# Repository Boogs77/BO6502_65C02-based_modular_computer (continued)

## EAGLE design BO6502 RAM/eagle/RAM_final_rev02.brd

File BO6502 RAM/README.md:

# BO6502 RAM Module

The **RAM Module** provides the primary volatile memory storage for the BO6502 system. This revision features a highly flexible addressing logic, allowing the user to map or exclude specific memory banks through a series of onboard jumpers.

---

## 🛠 Hardware Specifications

The module is designed to interface with the 6502 bus, providing fast access to 32KB of static RAM (SRAM).

* **Base Addressing:** By default, the module is mapped to the **$0000 - $7FFF** range. This is achieved by connecting the **A15** address line to the Enable pin of the decoder logic (active when A15 is Low).
* **Clock Synchronization:** The module typically triggers with the system clock to ensure data integrity during R/W cycles. However, **JP4** allows the user to set **IC2** as "Always Enabled," bypassing the system clock trigger for specific hardware configurations.

---

## 🕹️ Jumper Configuration & Memory Mapping

This module stands out for its versatility, managed through several jumper sets:

### I/O Exclusion Jumpers
The board includes **8 dedicated jumpers** designed to "carve out" space within the $0000 - $7FFF range. This allows other peripherals (such as I/O modules) to reside in that memory space without causing bus contention with the RAM.

### Address Bank Management
* **JP1 & JP2:** These jumpers allow the physical disconnection of **A13** and **A14** lines, useful for testing or specific memory mirroring configurations.
* **High-Memory Toggle:** A specific jumper configuration allows the RAM to be remapped to the **$8000 - $FFFF** range (High Memory) instead of its default Low Memory position.

---

## 📐 Board Layout & Rendering

The Revision 02 layout features optimized traces for high-speed signal integrity and clearly labeled jumper blocks for easy configuration.

---

## 📂 Related Modules
* 🏗️ **[Backplate System](https://github.com/Boogs77/BO6502/blob/main/BO6502%20BACKPLATE/README.md)**: 39-pin system bus connection.
* 🧠 **[CPU Module](https://github.com/Boogs77/BO6502/blob/main/BO6502%20CPU/README.md)**: W65C02 central processor.
* 🖥️ **[Monitor Interface](https://github.com/Boogs77/BO6502/blob/main/BO6502%20MONITOR/README.md)**: Recommended for debugging RAM read/write operations.

---
© 2026 Boogs77 | BO6502 Project - Technical Documentation.

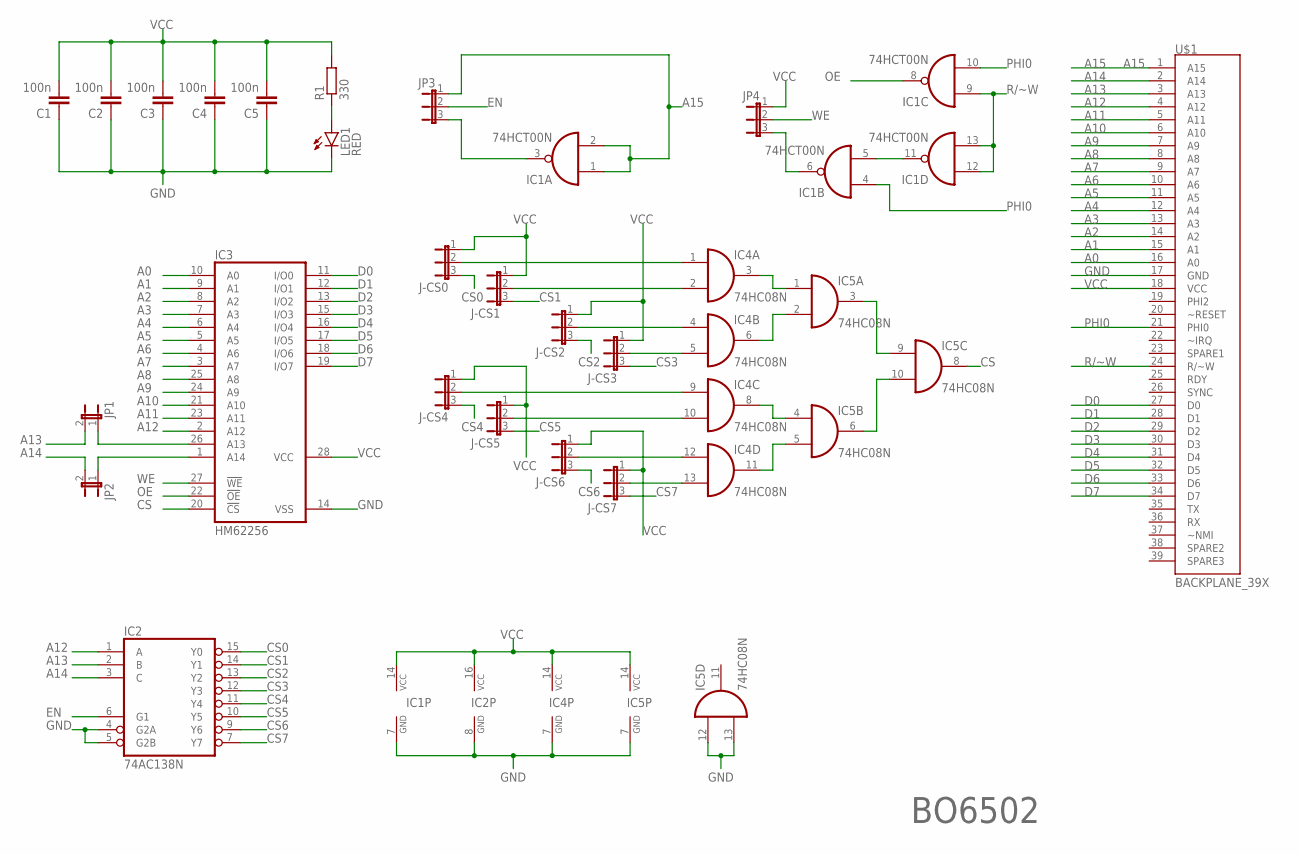
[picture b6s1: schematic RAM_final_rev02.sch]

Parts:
C1, C2, C3, C4, C5: 100n; C025-025X050
IC1: 74HCT00N; DIL14
IC2: 74AC138N; DIL16
IC3: HM62256; DIL28-6
IC4, IC5: 74HC08N; DIL14
J-CS0: J-CS0; JP2
J-CS1: J-CS1; JP2
J-CS2: J-CS2; JP2
J-CS3: J-CS3; JP2
J-CS4: J-CS4; JP2
J-CS5: J-CS5; JP2
J-CS6: J-CS6; JP2
J-CS7: J-CS7; JP2
JP1: JP1
JP2: JP2; JP1
JP3: JP3; JP2
JP4: JP4; JP2
LED1: RED; LED5MM
R1: 330; 0207/10
U$1: BACKPLANE_39X; BP_39X

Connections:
A0: IC3.10 (A0), U$1.16 (A0)
A1: IC3.9 (A1), U$1.15 (A1)
A2: IC3.8 (A2), U$1.14 (A2)
A3: IC3.7 (A3), U$1.13 (A3)
A4: IC3.6 (A4), U$1.12 (A4)
A5: IC3.5 (A5), U$1.11 (A5)
A6: IC3.4 (A6), U$1.10 (A6)
A7: IC3.3 (A7), U$1.9 (A7)
A8: IC3.25 (A8), U$1.8 (A8)
A9: IC3.24 (A9), U$1.7 (A9)
A10: IC3.21 (A10), U$1.6 (A10)
A11: IC3.23 (A11), U$1.5 (A11)
A12: IC2.1 (A), IC3.2 (A12), U$1.4 (A12)
A13: IC2.2 (B), JP1.2, U$1.3 (A13)
A14: IC2.3 (C), JP2.2, U$1.2 (A14)
A15: IC1.1 (I0), IC1.2 (I1), JP3.1, U$1.1 (A15)
CS: IC3.20 (!CS), IC5.8 (O)
CS0: IC2.15 (Y0), J-CS0.3
CS1: IC2.14 (Y1), J-CS1.3
CS2: IC2.13 (Y2), J-CS2.3
CS3: IC2.12 (Y3), J-CS3.3
CS4: IC2.11 (Y4), J-CS4.3
CS5: IC2.10 (Y5), J-CS5.3
CS6: IC2.9 (Y6), J-CS6.3
CS7: IC2.7 (Y7), J-CS7.3
D0: IC3.11 (I/O0), U$1.27 (D0)
D1: IC3.12 (I/O1), U$1.28 (D1)
D2: IC3.13 (I/O2), U$1.29 (D2)
D3: IC3.15 (I/O3), U$1.30 (D3)
D4: IC3.16 (I/O4), U$1.31 (D4)
D5: IC3.17 (I/O5), U$1.32 (D5)
D6: IC3.18 (I/O6), U$1.33 (D6)
D7: IC3.19 (I/O7), U$1.34 (D7)
EN: IC2.6 (G1), JP3.2
GND: C1.1, C2.1, C3.1, C4.1, C5.1, IC1.7 (GND), IC2.4 (G2A), IC2.5 (G2B), IC2.8 (GND), IC3.14 (VSS), IC4.7 (GND), IC5.7 (GND), IC5.12 (I0), IC5.13 (I1), LED1.K (C), U$1.17 (GND)
unnamed: IC3.26 (A13), JP1.1
unnamed: IC1.5 (I1), IC1.11 (O)
unnamed: IC1.3 (O), JP3.3
unnamed: IC1.6 (O), JP4.3
unnamed: IC4.3 (O), IC5.1 (I0)
unnamed: LED1.A, R1.1
unnamed: IC4.6 (O), IC5.2 (I1)
unnamed: IC4.8 (O), IC5.4 (I0)
unnamed: IC3.1 (A14), JP2.1
unnamed: IC4.11 (O), IC5.5 (I1)
unnamed: IC5.3 (O), IC5.9 (I0)
unnamed: IC5.6 (O), IC5.10 (I1)
unnamed: IC4.1 (I0), J-CS0.2
unnamed: IC4.2 (I1), J-CS1.2
unnamed: IC4.4 (I0), J-CS2.2
unnamed: IC4.5 (I1), J-CS3.2
unnamed: IC4.9 (I0), J-CS4.2
unnamed: IC4.10 (I1), J-CS5.2
unnamed: IC4.12 (I0), J-CS6.2
unnamed: IC4.13 (I1), J-CS7.2
OE: IC1.8 (O), IC3.22 (!OE)
PHI0: IC1.4 (I0), IC1.10 (I1), U$1.21 (PHI0)
R/~W: IC1.9 (I0), IC1.12 (I0), IC1.13 (I1), U$1.24 (R/~W)
VCC: C1.2, C2.2, C3.2, C4.2, C5.2, IC1.14 (VCC), IC2.16 (VCC), IC3.28 (VCC), IC4.14 (VCC), IC5.14 (VCC), J-CS0.1, J-CS1.1, J-CS2.1, J-CS3.1, J-CS4.1, J-CS5.1, J-CS6.1, J-CS7.1, JP4.1, R1.2, U$1.18 (VCC)
WE: IC3.27 (!WE), JP4.2

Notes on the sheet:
BO6502

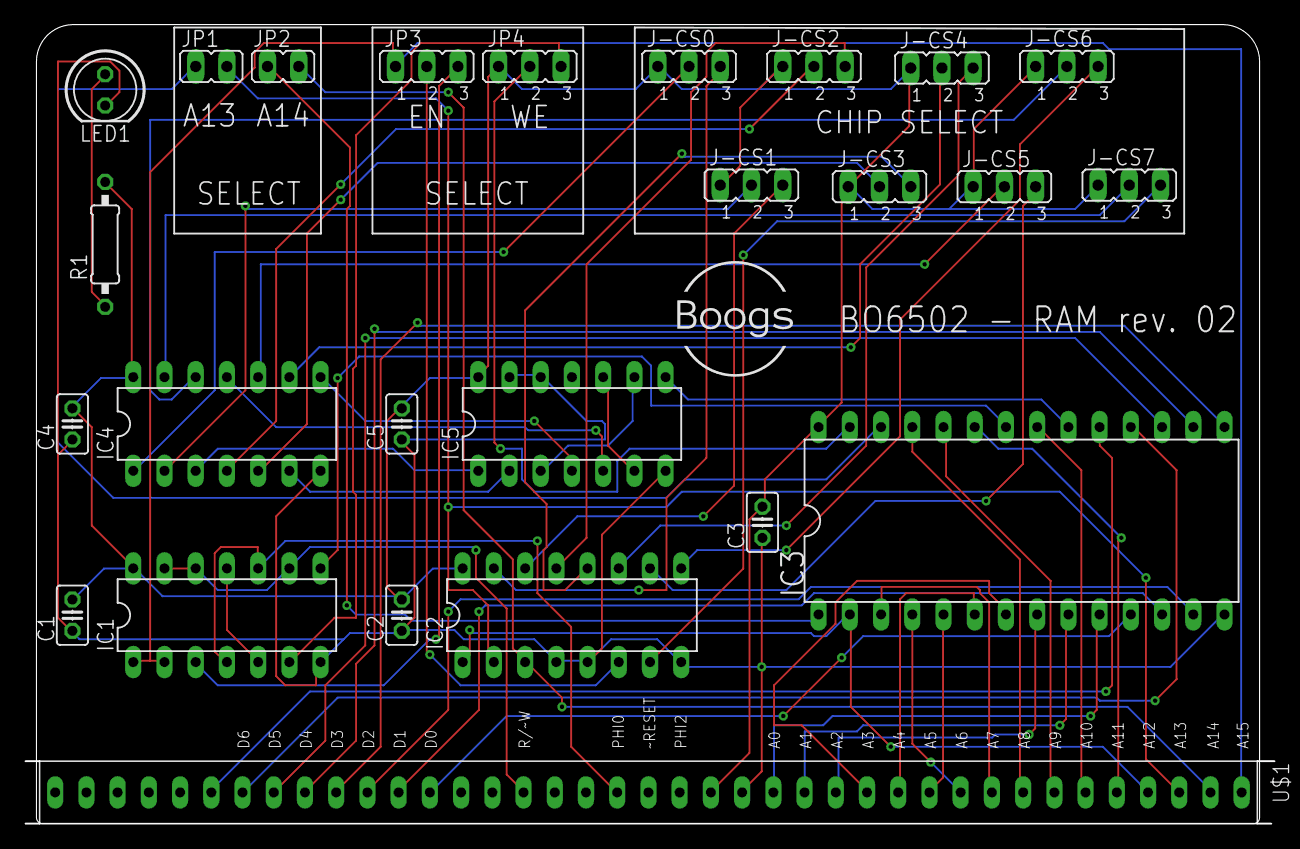
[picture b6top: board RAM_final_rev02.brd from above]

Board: 2 copper layers, 101.6 x 65.0 mm, 25 parts (0 on the bottom side), 60 nets.

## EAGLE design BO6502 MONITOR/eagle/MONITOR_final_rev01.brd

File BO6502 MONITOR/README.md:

# BO6502 Monitor Interface

The **Monitor Interface** is a diagnostic tool designed to provide real-time visibility into the internal operations of the BO6502 system. By interfacing an **Arduino Mega**, it allows the user to inspect the Address Bus and Data Bus during execution.

---

## 🛠 Operation & Hardware Setup

This module is specifically conceived for debugging at very low clock frequencies (manual pulsing or slow-stepping). It is designed to work in conjunction with an external clock source, such as the **[6502 Clock Module by dbuchewald](https://github.com/dbwald/6502/tree/master/Schematics/Clock_module)**.

* **Controller:** The board features a socket for an **Arduino Mega**, which acts as the logic analyzer.
* **Bus Monitoring:** It captures the state of the 16-bit Address Bus and the 8-bit Data Bus.
* **Triggering:** The monitoring logic is synchronized with the system clock signal connected to an Arduino interrupt pin.
* **Power Management:** A **dedicated jumper** has been included in the design. This allows the user to choose whether to power the Arduino Mega from the system bus or to isolate it when using an **external power source**, preventing potential power conflicts.

---

## 💻 Logic & Firmware

The monitoring principle follows the implementation popularized by **Ben Eater**. The firmware triggers a read cycle on every **rising edge** of the clock.

* **Firmware Reference:** **[6502-monitor.ino](https://eater.net/downloads/6502-monitor.ino)**.
* **Mechanism:** When the clock signal goes high, the Arduino triggers an interrupt service routine (ISR) to sample the address and data lines instantly, formatting the output for the Serial Monitor (Hexadecimal/Binary).

---

## 🕹️ Addressing & Compatibility

Since this module acts as a passive listener (sniffer) on the bus, it does not require a specific I/O address range (like $DXXX) and does not interfere with the system's memory mapping.

> [!IMPORTANT]
> This module is intended for **low-speed diagnostics only**. Due to the sampling latency of the Arduino Mega, it cannot monitor the bus accurately at the full 1MHz+ speeds of the 65C02.

---

## 📐 Board Layout & Rendering

The board provides clean routing for the 39-pin system bus directly to the Arduino Mega digital headers.

---

## 📂 Related Modules
* 🏗️ **[Backplate System](https://github.com/Boogs77/BO6502/blob/main/BO6502%20BACKPLATE/README.md)**: Main 39-pin system bus connection.
* 🧠 **[CPU Module](https://github.com/Boogs77/BO6502/blob/main/BO6502%20CPU/README.md)**: W65C02 central processor.
* 🔴 **[LED Test Board](https://github.com/Boogs77/BO6502/blob/main/BO6502%20LED/README.md)**: Alternative visual diagnostic tool.

---
© 2026 Boogs77 | BO6502 Project - Technical Documentation.

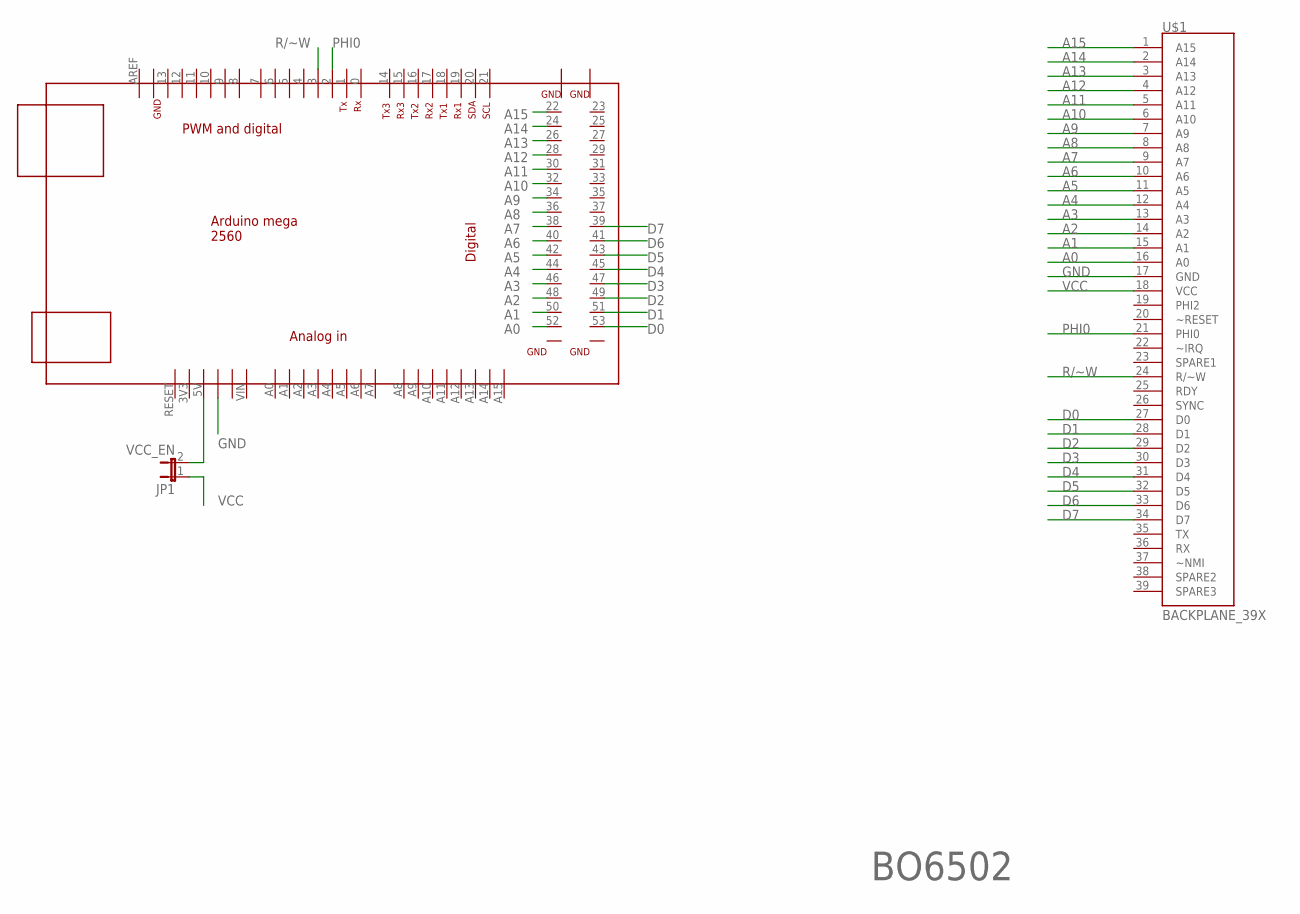
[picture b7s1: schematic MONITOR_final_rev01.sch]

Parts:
JP1: VCC_EN; JP1
U$1: BACKPLANE_39X; BP_39X
U$2: MEGA_DEVICE; MEGAOUTLINE

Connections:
A0: U$1.16 (A0), U$2.52
A1: U$1.15 (A1), U$2.50
A2: U$1.14 (A2), U$2.48
A3: U$1.13 (A3), U$2.46
A4: U$1.12 (A4), U$2.44
A5: U$1.11 (A5), U$2.42
A6: U$1.10 (A6), U$2.40
A7: U$1.9 (A7), U$2.38
A8: U$1.8 (A8), U$2.36
A9: U$1.7 (A9), U$2.34
A10: U$1.6 (A10), U$2.32
A11: U$1.5 (A11), U$2.30
A12: U$1.4 (A12), U$2.28
A13: U$1.3 (A13), U$2.26
A14: U$1.2 (A14), U$2.24
A15: U$1.1 (A15), U$2.22
D0: U$1.27 (D0), U$2.53
D1: U$1.28 (D1), U$2.51
D2: U$1.29 (D2), U$2.49
D3: U$1.30 (D3), U$2.47
D4: U$1.31 (D4), U$2.45
D5: U$1.32 (D5), U$2.43
D6: U$1.33 (D6), U$2.41
D7: U$1.34 (D7), U$2.39
GND: U$1.17 (GND), U$2.GND@2 (GND)
unnamed: JP1.2, U$2.5V
PHI0: U$1.21 (PHI0), U$2.2
R/~W: U$1.24 (R/~W), U$2.3
VCC: JP1.1, U$1.18 (VCC)

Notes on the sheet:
BO6502

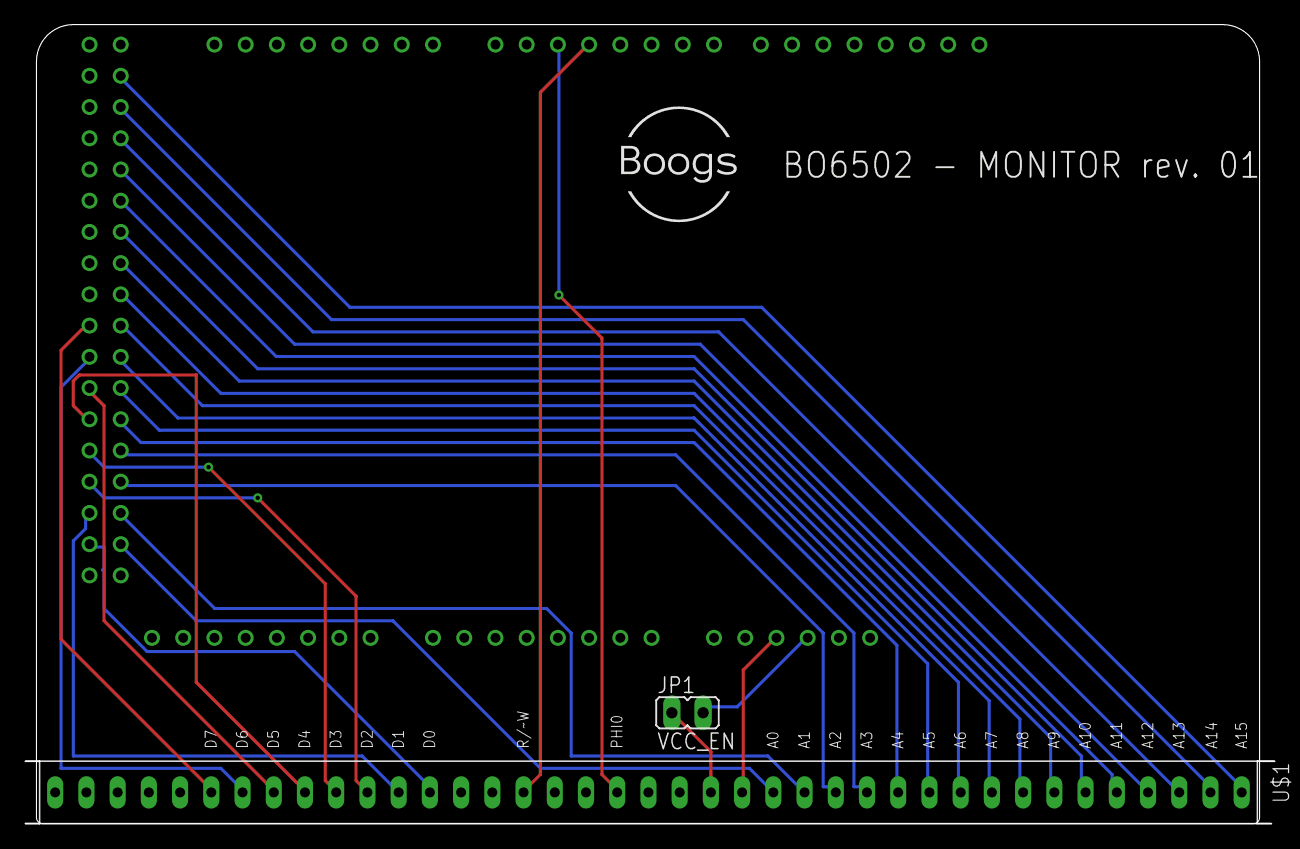
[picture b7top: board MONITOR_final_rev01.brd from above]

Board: 2 copper layers, 101.6 x 65.0 mm, 3 parts (1 on the bottom side), 29 nets.

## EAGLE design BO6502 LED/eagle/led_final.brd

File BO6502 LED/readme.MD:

# BO6502 LED Test Board

The **LED Test Board** is a specialized diagnostic module designed to verify the operational functionality of the **W65C22 VIA** (Versatile Interface Adapter) and to monitor bus activity through visual feedback.

---

## 🛠 Hardware Specifications

This board serves as a hardware debugger and training tool for the BO6502 system. It allows for real-time visualization of the VIA port states.

* **LED Array:** Features 16 independent LEDs connected directly to the VIA I/O ports.
* **Port Mapping:** * **Port A (PA0-PA7):** Controls the first bank of 8 LEDs.
    * **Port B (PB0-PB7):** Controls the second bank of 8 LEDs.
* **Purpose:** Ideal for testing bit-banging routines, interrupt handling, and basic I/O operations before deploying more complex modules.

---

## 🕹️ Addressing & Compatibility Warning ($DXXX)

The module utilizes a broad addressing scheme for the W65C22 VIA, mapping it across the **$DXXX** memory interval.

> [!CAUTION]
> **Compatibility Note:** Due to the partial address decoding (using the entire $DXXX range), this board is **not compatible** with many other configurations and modules in the BO6502 project that occupy specific sub-ranges within the same space. It is primarily intended for standalone testing or minimal system configurations.

---

## 📐 Board Layout & Rendering

The layout is optimized for visibility, with the LED banks clearly labeled to match the corresponding VIA pins.

---

## 🖥️ Programming Guide

To light up the LEDs, the Data Direction Registers (DDR) must be configured as outputs.

```assembly
; BO6502 LED Test Code
LDA #$FF
STA $D002    ; Set DDRB as Output
STA $D003    ; Set DDRA as Output

LOOP:
    INC $D000 ; Increment Port B LEDs
    INC $D001 ; Increment Port A LEDs
    JMP LOOP

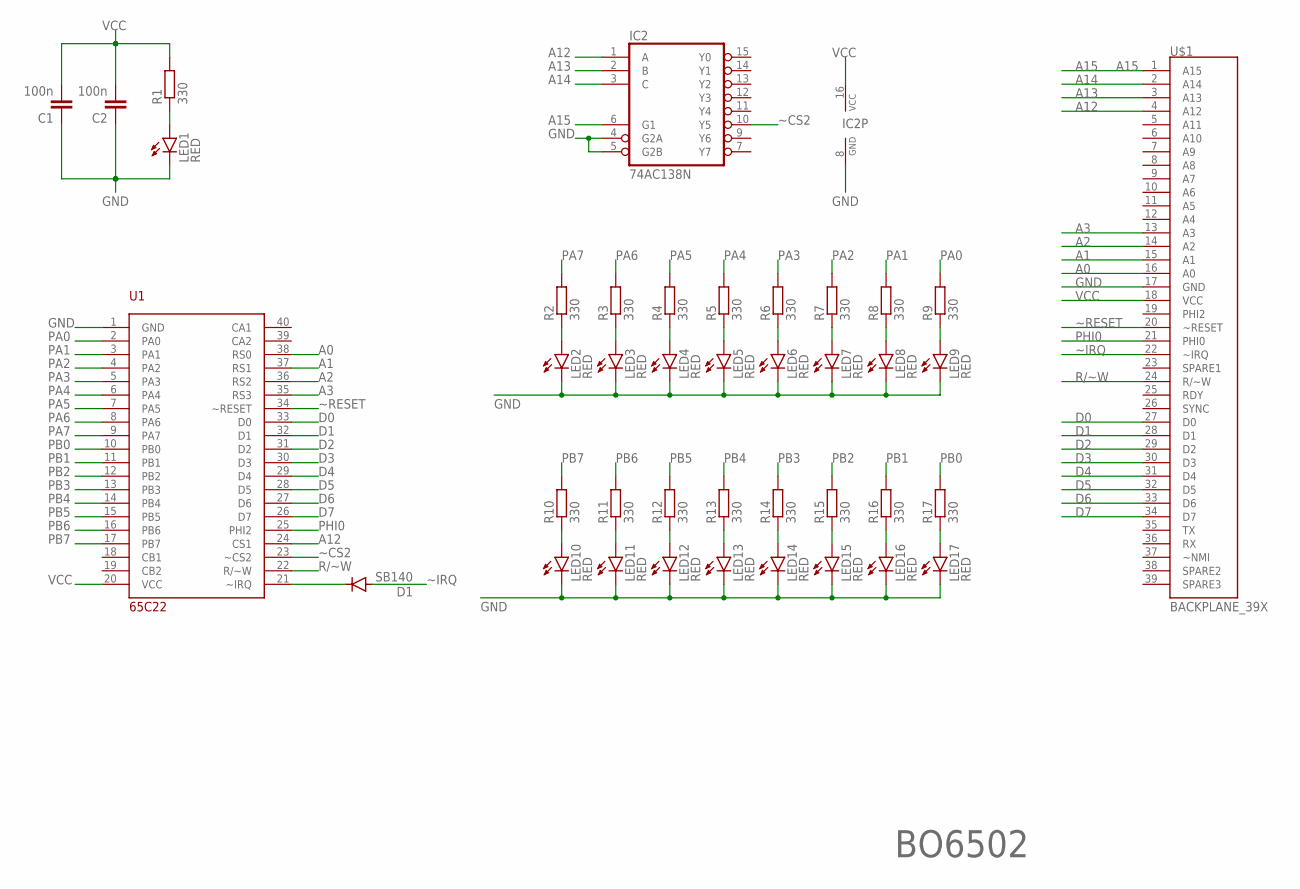
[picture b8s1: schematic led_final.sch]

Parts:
C1, C2: 100n; C025-025X050
D1: SB140; DO41-10
IC2: 74AC138N; DIL16
LED1, LED2, LED3, LED4, LED5, LED6, LED7, LED8, LED9, LED10, LED11, LED12, LED13, LED14, LED15, LED16, LED17: RED; LED5MM
R1, R2, R3, R4, R5, R6, R7, R8, R9, R10, R11, R12, R13, R14, R15, R16, R17: 330; 0207/10
U1: 65C22; DIL40
U$1: BACKPLANE_39X; BP_39X

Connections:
A0: U1.38 (RS0), U$1.16 (A0)
A1: U1.37 (RS1), U$1.15 (A1)
A2: U1.36 (RS2), U$1.14 (A2)
A3: U1.35 (RS3), U$1.13 (A3)
A12: IC2.1 (A), U1.24 (CS1), U$1.4 (A12)
A13: IC2.2 (B), U$1.3 (A13)
A14: IC2.3 (C), U$1.2 (A14)
A15: IC2.6 (G1), U$1.1 (A15)
D0: U1.33 (D0), U$1.27 (D0)
D1: U1.32 (D1), U$1.28 (D1)
D2: U1.31 (D2), U$1.29 (D2)
D3: U1.30 (D3), U$1.30 (D3)
D4: U1.29 (D4), U$1.31 (D4)
D5: U1.28 (D5), U$1.32 (D5)
D6: U1.27 (D6), U$1.33 (D6)
D7: U1.26 (D7), U$1.34 (D7)
GND: C1.1, C2.1, IC2.4 (G2A), IC2.5 (G2B), IC2.8 (GND), LED1.K (C), LED2.K (C), LED3.K (C), LED4.K (C), LED5.K (C), LED6.K (C), LED7.K (C), LED8.K (C), LED9.K (C), LED10.K (C), LED11.K (C), LED12.K (C), LED13.K (C), LED14.K (C), LED15.K (C), LED16.K (C), LED17.K (C), U1.1 (GND), U$1.17 (GND)
unnamed: D1.C, U1.21 (~IRQ)
unnamed: LED2.A, R2.1
unnamed: LED3.A, R3.1
unnamed: LED1.A, R1.1
unnamed: LED4.A, R4.1
unnamed: LED5.A, R5.1
unnamed: LED6.A, R6.1
unnamed: LED7.A, R7.1
unnamed: LED8.A, R8.1
unnamed: LED9.A, R9.1
unnamed: LED10.A, R10.1
unnamed: LED11.A, R11.1
unnamed: LED12.A, R12.1
unnamed: LED13.A, R13.1
unnamed: LED14.A, R14.1
unnamed: LED15.A, R15.1
unnamed: LED16.A, R16.1
unnamed: LED17.A, R17.1
PA0: R9.2, U1.2 (PA0)
PA1: R8.2, U1.3 (PA1)
PA2: R7.2, U1.4 (PA2)
PA3: R6.2, U1.5 (PA3)
PA4: R5.2, U1.6 (PA4)
PA5: R4.2, U1.7 (PA5)
PA6: R3.2, U1.8 (PA6)
PA7: R2.2, U1.9 (PA7)
PB0: R17.2, U1.10 (PB0)
PB1: R16.2, U1.11 (PB1)
PB2: R15.2, U1.12 (PB2)
PB3: R14.2, U1.13 (PB3)
PB4: R13.2, U1.14 (PB4)
PB5: R12.2, U1.15 (PB5)
PB6: R11.2, U1.16 (PB6)
PB7: R10.2, U1.17 (PB7)
PHI0: U1.25 (PHI2), U$1.21 (PHI0)
R/~W: U1.22 (R/~W), U$1.24 (R/~W)
VCC: C1.2, C2.2, IC2.16 (VCC), R1.2, U1.20 (VCC), U$1.18 (VCC)
~CS2: IC2.10 (Y5), U1.23 (~CS2)
~IRQ: D1.A, U$1.22 (~IRQ)
~RESET: U1.34 (~RESET), U$1.20 (~RESET)

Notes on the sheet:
BO6502

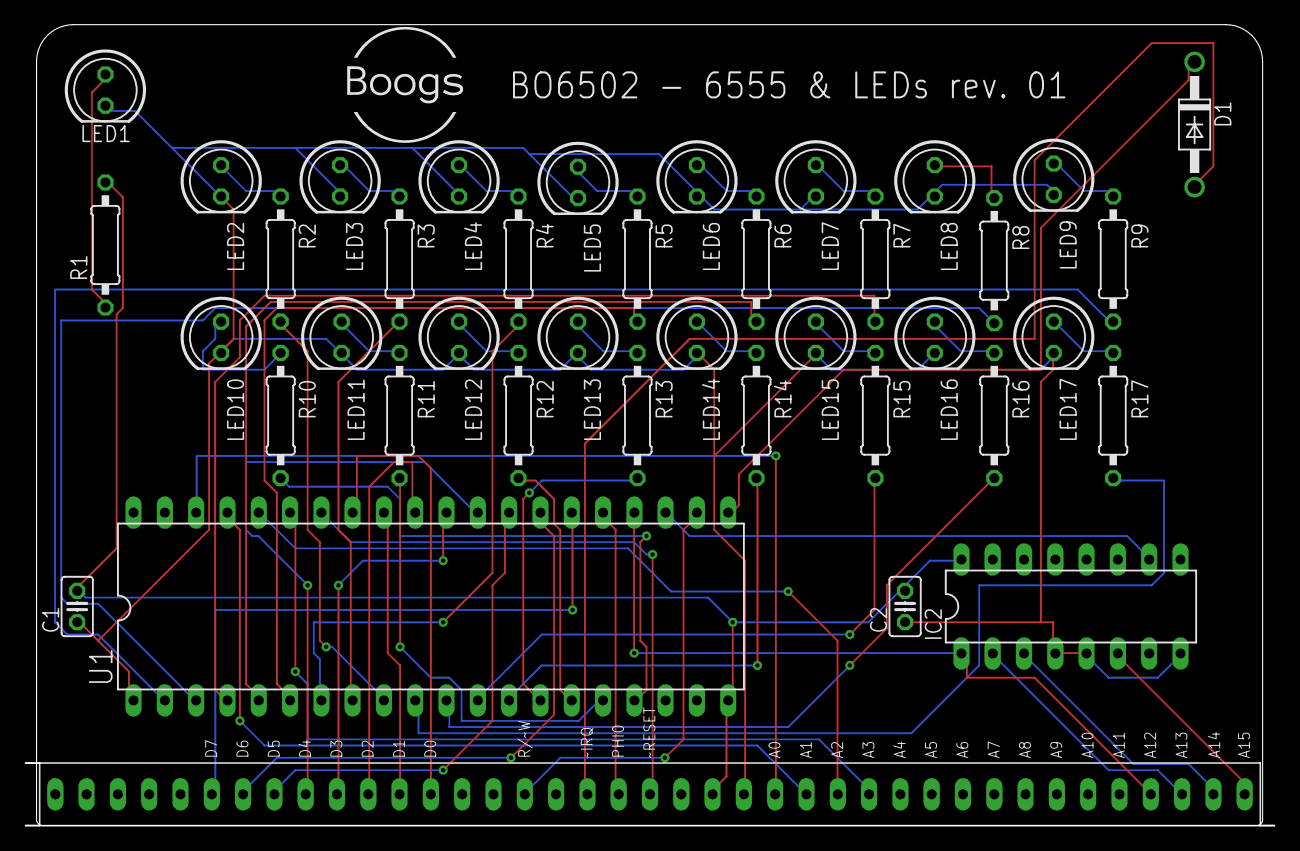
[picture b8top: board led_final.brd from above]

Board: 2 copper layers, 101.3 x 65.0 mm, 40 parts (0 on the bottom side), 57 nets.

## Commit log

2026-01-30 move
2026-01-31 picture changes
2026-01-31 Add README for BO6502 backplate
2026-01-31 Add backplate_final_rev02 section to README
2026-01-31 Update backplate_final_rev02 formatting in README
2026-01-31 Update README to clarify voltage regulator details
2026-01-31 Update README with backplate details and formatting
    Corrected formatting and added details about backplate revisions.
2026-01-31 few changes
2026-01-31 main changes
2026-02-01 many changes
2026-02-01 Changes images pcb color
2026-02-01 Audio changes
2026-02-01 change name
2026-02-01 Add KEYB PCB
2026-02-01 Rename readme.MD to README.md
2026-02-01 PCB LEDs changes
2026-02-01 Add monitor PCB
2026-02-01 add RAM PCB
2026-02-01 Add RESET PCB
2026-02-01 add rom PCBs
2026-02-02 add SDCard PCB
2026-02-02 add SERIAL PCB
2026-02-02 add VDU PCB
2026-02-02 final README.md
2026-05-17 Update README to remove citation markers
    Removed citation markers from the technical overview.
2026-05-17 Remove citation markers from README.md
